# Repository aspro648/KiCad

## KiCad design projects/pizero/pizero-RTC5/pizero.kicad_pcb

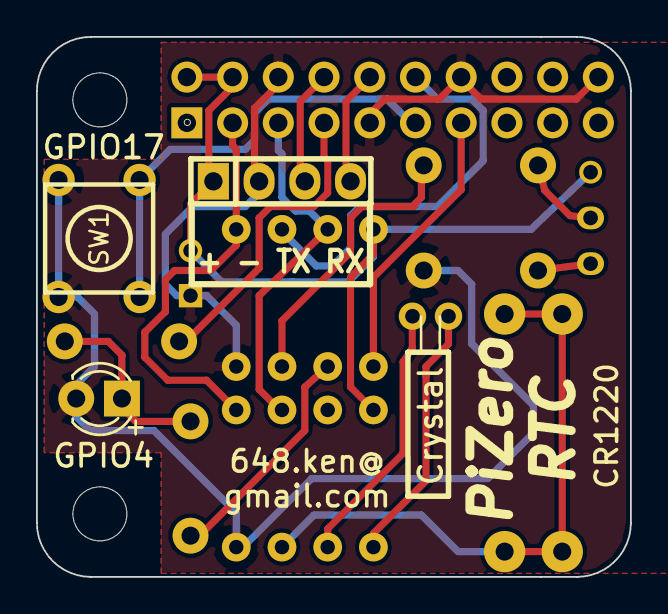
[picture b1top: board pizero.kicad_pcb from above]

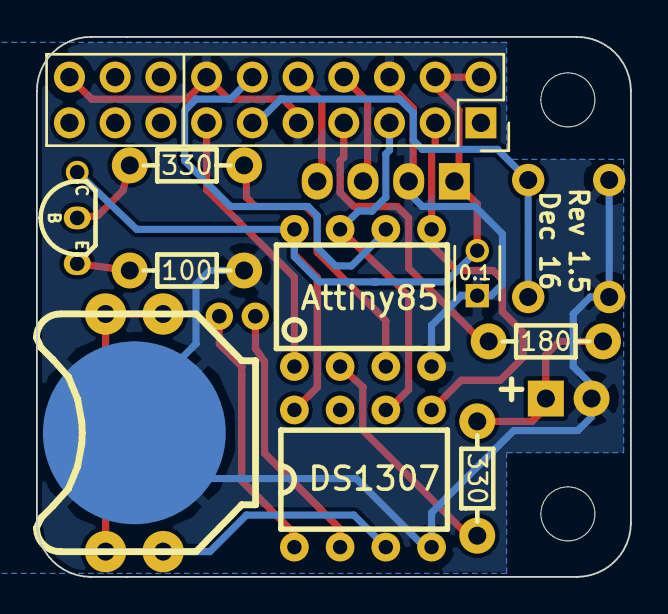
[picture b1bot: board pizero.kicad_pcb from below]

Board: 2 copper layers, 33.0 x 30.0 mm, 15 parts (10 on the bottom side), 18 nets.

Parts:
0.1: C_Small; C_Disc_D3_P2.5
32.768: Crystal; Crystal_Watch
BT1: Battery; BATT_12mm_TH
D1: LED; LED-3MM
IC1: ATTINY85-S; DIP-8_W7.62mm
P1: CONN_01X04; Pin_Header_Straight_1x04
P2: CONN_01X01; Pin_Header_Straight_1x01
P3: Raspberry_Pi_+_Conn; Pin_Header_Straight_2x10
Q1: Q_NPN_EBC; TO-92_NPN_EBC_wide
R1: 180; Resistor_Horz
R2, R3: 330; Resistor_Horz
R4: 100; Resistor_Horz
SW1: SPST; SW_PUSH_SMALL
U1: DS1307; DIP-8_W7.62mm

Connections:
GND: 0.1.1, BT1.2, D1.1, IC1.4, P1.2, P3.6, P3.9, P3.14, P3.20, R4.2, SW1.2, U1.4
unnamed: 32.768.1, U1.1
unnamed: 32.768.2, U1.2
unnamed: BT1.1, U1.3
unnamed: D1.2, R1.1, R2.1
unnamed: IC1.1, P3.13
unnamed: IC1.2, R2.2
unnamed: IC1.3, R3.1
unnamed: IC1.5, P3.3, U1.5
unnamed: IC1.6, P3.12
unnamed: IC1.7, P3.5, U1.6
unnamed: P1.3, P3.8
unnamed: P1.4, P3.10
unnamed: P3.7, R1.2
unnamed: P3.11, SW1.1
unnamed: Q1.1, R4.1
unnamed: Q1.2, R3.2
VCC: 0.1.2, IC1.8, P1.1, P3.2, P3.4, Q1.3, U1.8

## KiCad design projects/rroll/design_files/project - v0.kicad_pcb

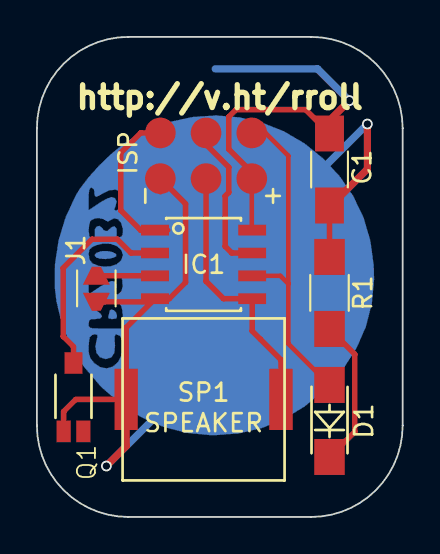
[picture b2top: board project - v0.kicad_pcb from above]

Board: 2 copper layers, 20.3 x 26.7 mm, 9 parts (1 on the bottom side), 9 nets.

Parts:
BT1: Battery; BATT_CR2032_SMD
C1: 0.1 uF; C_1206_HandSoldering
CON1: ISP; Pin_Header_Straight_2x03_Pitch2.54mm
D1: LED; LED_1206_HandSoldering
IC1: ATTINY85; SOIC-8_3.9x4.9mm_Pitch1.27mm
J1: JMP; R_1206_HandSoldering
Q1: LIGHT; PHOTO_TRANS
R1: 330; R_1206_HandSoldering
SP1: SPEAKER; PS1240_piezo

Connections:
+BATT: BT1.1, C1.2, CON1.2, IC1.8
GND: BT1.2, C1.1, CON1.6, IC1.4, J1.1, Q1.1, R1.1, SP1.1
unnamed: CON1.1, D1.2, IC1.6
unnamed: CON1.3, IC1.7
unnamed: CON1.4, IC1.5, SP1.2
unnamed: CON1.5, IC1.1
unnamed: D1.1, R1.2
unnamed: IC1.2, Q1.3
unnamed: IC1.3, J1.2

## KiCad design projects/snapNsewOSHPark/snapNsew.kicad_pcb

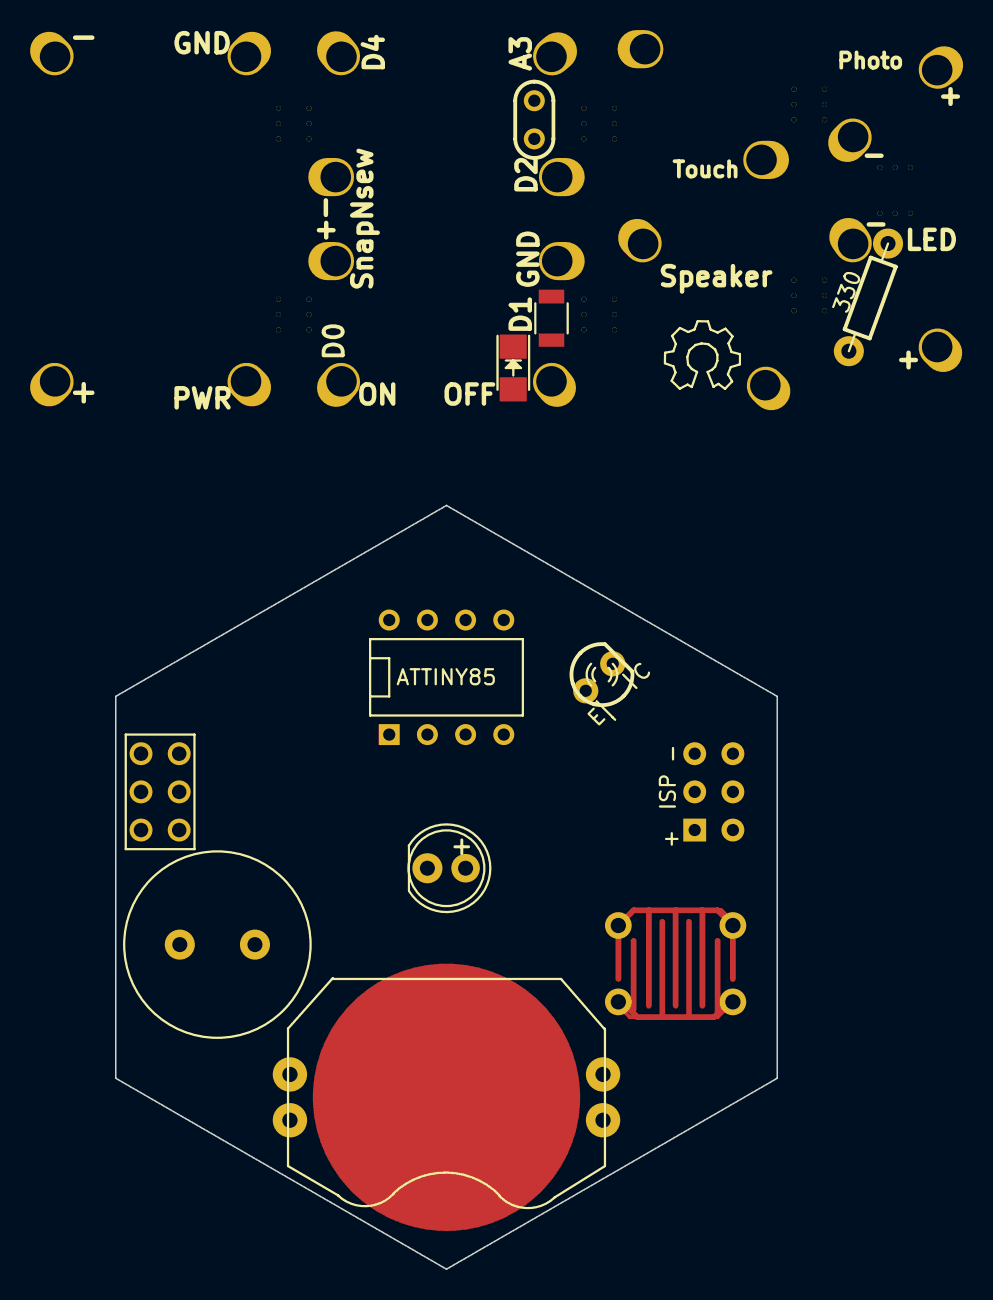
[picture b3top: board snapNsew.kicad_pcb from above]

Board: 2 copper layers, 44.0 x 50.8 mm, 33 parts (0 on the bottom side), 11 nets, no tracks yet.

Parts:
BT1: Battery; BATT_CR2032
C1: 0.1 uF; C1
CON1: ISP; myISP
D1: LED; LED-1206
D3: LED; LED-5MM
GND1, GND2, GND3, GND4: CONN_01X01; SEWPAD
IC1: ATTINY85; DIP-8__300
L1, L2: CONN_01X01; SEWPAD
P0, P1, P2, P3, P4: CONN_01X01; SEWPAD
PWR1, PWR2, PWR3: CONN_01X01; SEWPAD
Q1: LIGHT; PHOTO_TRANS
R1: 330; R_1206
R4: 330; Resistor_Horizontal_RM10mm
S1, S2: CONN_01X01; SEWPAD
SP1: SPEAKER; PS1240_piezo
SW1: SPST; mySwitchDPDT
T1, T2: CONN_01X01; SEWPAD
TOUCH1: SW_PUSH; SW_PUSH_TOUCH
VAL: MadeInOregonRev25
Z1, Z2: CONN_01X01; SEWPAD

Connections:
+BATT: C1.2, CON1.2, IC1.8, SW1.2
GND: BT1.2, C1.1, CON1.6, GND1.1, GND2.1, GND3.1, GND4.1, IC1.4, L2.1, Q1.1, R1.1, R4.1, S2.1, SP1.1, T2.1, TOUCH1.2, Z2.1
unnamed: BT1.1, PWR1.1, PWR2.1, PWR3.1, SW1.1
unnamed: CON1.1, D1.2, IC1.6, P1.1
unnamed: CON1.3, IC1.7, P2.1, T1.1, TOUCH1.1
unnamed: CON1.4, IC1.5, P0.1, S1.1, SP1.2
unnamed: CON1.5, IC1.1
unnamed: D1.1, R1.2
unnamed: D3.1, R4.2
unnamed: D3.2, IC1.3, P4.1, Z1.1
unnamed: IC1.2, L1.1, P3.1, Q1.3

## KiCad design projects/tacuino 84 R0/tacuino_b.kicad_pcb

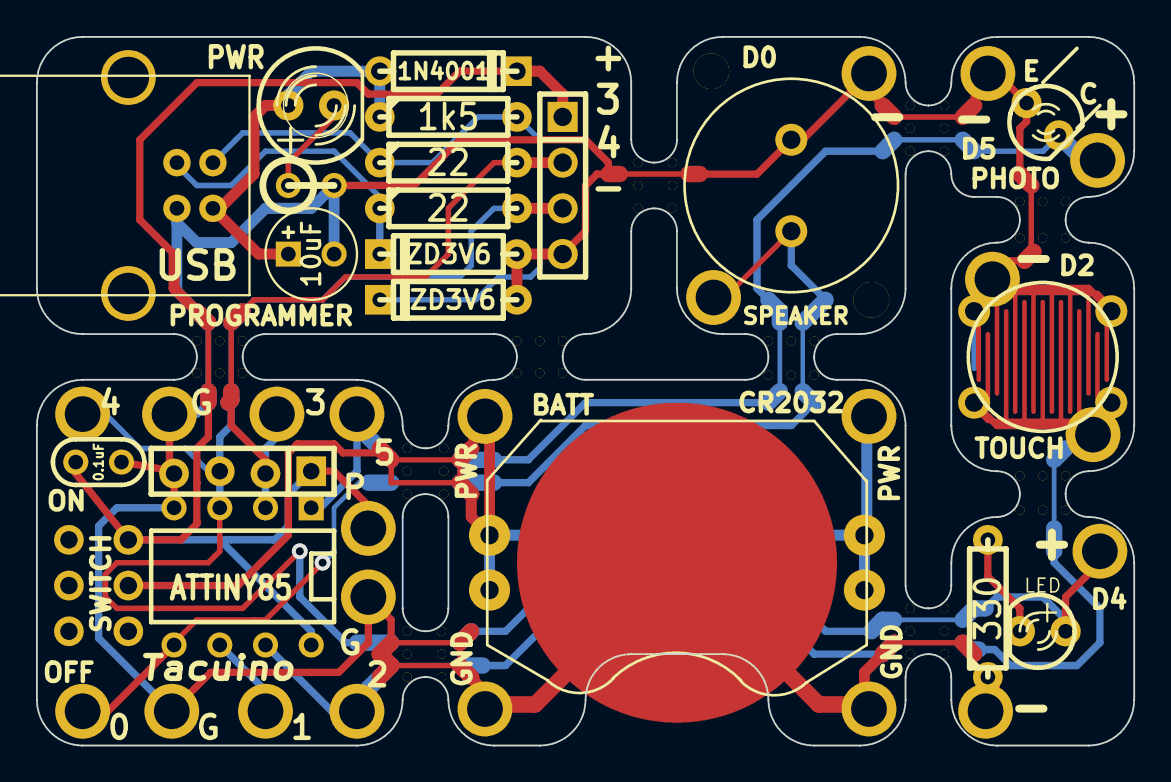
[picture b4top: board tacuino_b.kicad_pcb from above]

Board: 2 copper layers, 61.0 x 39.4 mm, 66 parts (0 on the bottom side), 14 nets.

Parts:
1N4001: DIODE; D3
BT1: BATTERY; BATT_CR2032
B_C1: 1pin-Sew-thin
B_C2: CONN_1; 1pin-Sew-thin
B_N1, B_N2: GND; 1pin-Sew-thin
B_P1, B_P2: PWR; 1pin-Sew-thin
C1: 0.1uF; C1
C2: 10uF; C1V5
D2: PWR; LED-5MM
D3, D5: ZD3V6; D3
D4: LED; LED-3MM
HOLE_1, HOLE_2: CONN_1; 078hole
IC1: ATTINY85; DIP-8__300
J1: USB; USB_B
L1_C1, L1_C2: 1pin-Sew-thin
OSHW_r_silk_23: OSHW_r_silk_23
P1, P2: CONN_4; SIL-4
PD0: 0; 1pin-Sew-thin
PD1: 1; 1pin-Sew-thin
PD2: 2; 1pin-Sew-thin
PD3: 3; 1pin-Sew-thin
PD4: 4; 1pin-Sew-thin
PD5: 5; 1pin-Sew-thin
PDGND1, PDGND2, PDGND3: G; 1pin-Sew-thin
PDVCC1: P; 1pin-Sew-thin
P_1, P_2: 1pin-Sew-thin
Q1: PHOTO; LED-3MM
R1: 330; R3-LARGE_PADS
R2: 1k5; R3-LARGE_PADS
R3, R4: 22; R3-LARGE_PADS
R6: 330; R1
SP1: SPEAKER
SW1: TOUCH; SW_PUSH_TOUCH
SW2: ON; SW_SPST
S_C1, S_C2: 1pin-Sew-thin
p: P; 3hole_mousebite
p#2, p#3, p#4, p#5, p#6, p#7, p#8, p#9, p#10, p#11, p#12, p#13, p#14, p#15, p#16, p#17, p#18, p#19, p#20: P; 3hole_mousebite

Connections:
+5V: 1N4001.1, C2.1, D2.1, J1.1, R2.1
+BATT: 1N4001.2, C1.1, IC1.8, P1.1, P2.1, PDVCC1.1, SW2.1
GND: BT1.2, B_C1.1, B_C2.1, B_N1.1, B_N2.1, C1.2, C2.2, D3.1, D5.1, IC1.4, J1.4, L1_C1.1, P1.4, P2.4, PDGND1.1, PDGND2.1, PDGND3.1, P_1.1, Q1.1, R1.1, R6.2, SP1.1, SW1.2
unnamed: BT1.1, B_P1.1, B_P2.1, SW2.2
unnamed: IC1.7, PD2.1, SW1.1, S_C2.1
unnamed: IC1.1, PD5.1, P_2.1, Q1.2
unnamed: D2.2, R6.1
unnamed: D5.2, J1.2, R2.2, R4.1
unnamed: D4.1, IC1.3, L1_C2.1, P1.3, P2.3, PD4.1, R3.2
unnamed: IC1.5, PD0.1, SP1.2, S_C1.1
unnamed: IC1.6, PD1.1
unnamed: IC1.2, P1.2, P2.2, PD3.1, R4.2
unnamed: D3.2, J1.3, R3.1
unnamed: D4.2, R1.2

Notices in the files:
projects/pizero/pizero-RTC5/pizero.kicad_pcb:
License: CERN OHL V1.2
